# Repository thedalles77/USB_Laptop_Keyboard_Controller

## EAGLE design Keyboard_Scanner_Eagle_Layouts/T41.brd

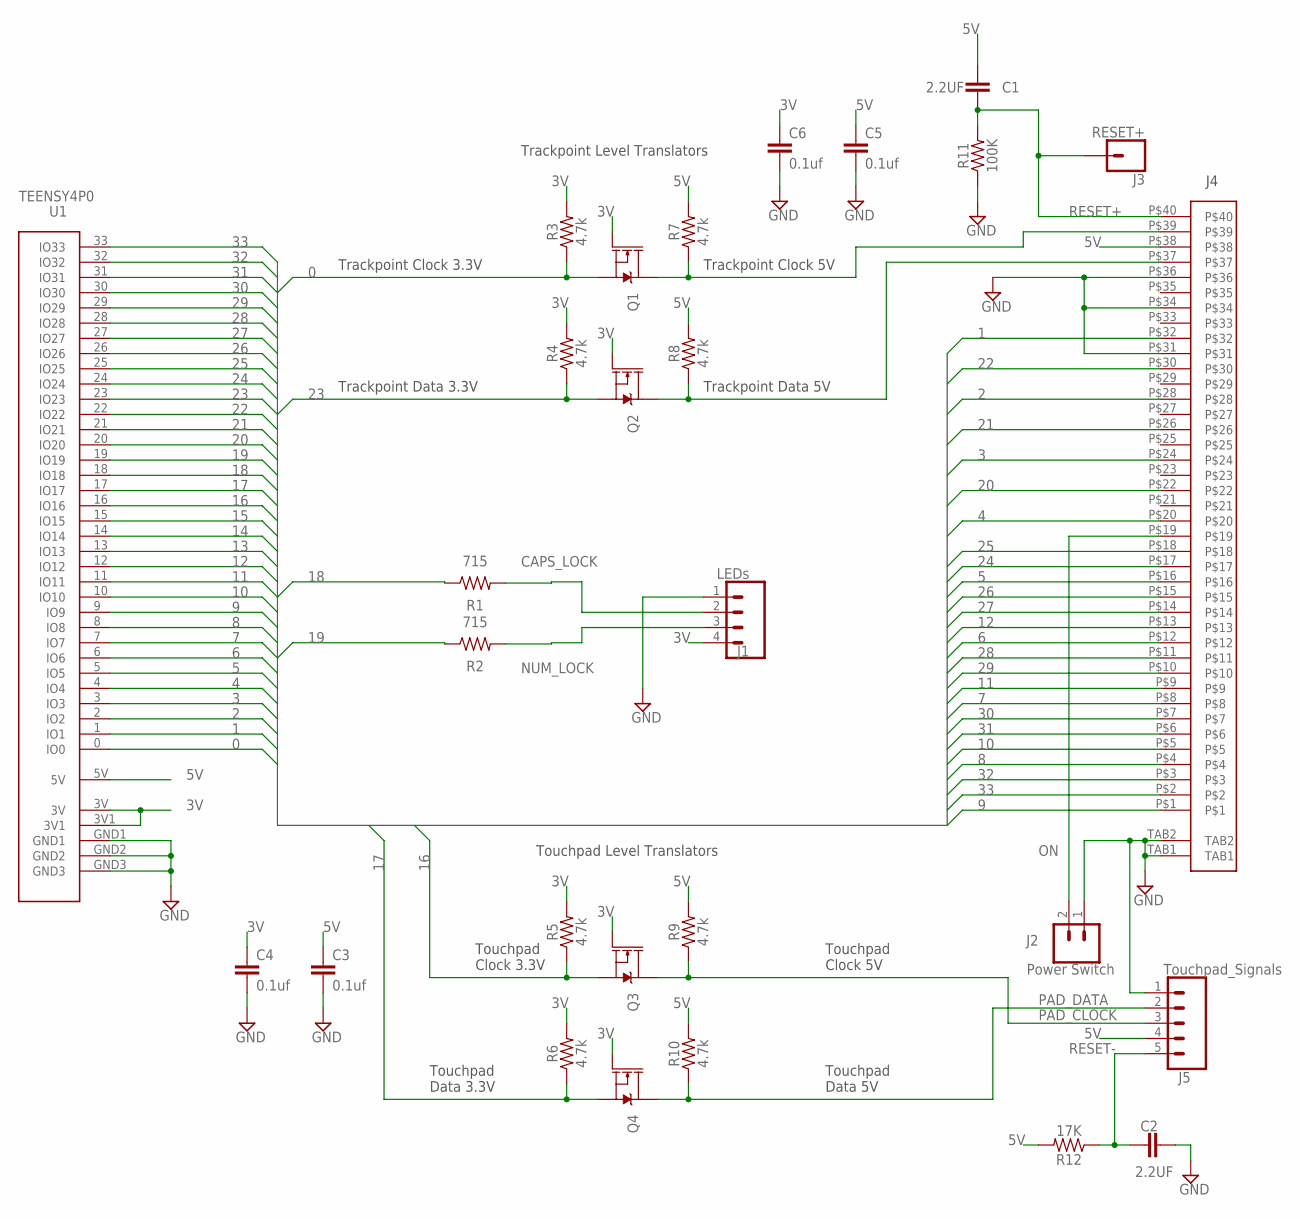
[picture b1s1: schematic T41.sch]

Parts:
C1, C2: 2.2UF; 0603_CAP
C3, C4, C5, C6: 0.1uf; 0603_CAP
J1: LEDs; 1X04
J2: Power Switch; 1X02
J3: RESET+; 1X01_NO_SILK
J4: KX14-40K5DE; KX14_40K5DE
J5: Touchpad_Signals; 1X05
Q1, Q2, Q3, Q4: 220mA/50V/3.5Ω; SOT23-3
R1, R2: 715; 0603
R3, R4, R5, R6, R7, R8, R9, R10: 4.7k; 0603
R11: 100K; 0603_RESISTOR
R12: 17K; 0603_RESISTOR
U1: TEENSY4P0

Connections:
0: Q1.2 (S), R3.1, U1.0 (IO0)
1: J4.P$32, U1.1 (IO1)
2: J4.P$28, U1.2 (IO2)
3: J4.P$24, U1.3 (IO3)
3V: C4.1, C6.1, J1.4, Q1.1 (G), Q2.1 (G), Q3.1 (G), Q4.1 (G), R3.2, R4.2, R5.2, R6.2, U1.3V, U1.3V1
4: J4.P$20, U1.4 (IO4)
5: J4.P$16, U1.5 (IO5)
5V: C1.1, C3.1, C5.1, J4.P$38, J5.4, R7.2, R8.2, R9.2, R10.2, R12.2, U1.5V
6: J4.P$12, U1.6 (IO6)
7: J4.P$8, U1.7 (IO7)
8: J4.P$4, U1.8 (IO8)
9: J4.P$1, U1.9 (IO9)
10: J4.P$5, U1.10 (IO10)
11: J4.P$9, U1.11 (IO11)
12: J4.P$13, U1.12 (IO12)
13: U1.13 (IO13)
14: U1.14 (IO14)
15: U1.15 (IO15)
16: Q3.2 (S), R5.1, U1.16 (IO16)
17: Q4.2 (S), R6.1, U1.17 (IO17)
18: R1.1, U1.18 (IO18)
19: R2.1, U1.19 (IO19)
20: J4.P$22, U1.20 (IO20)
21: J4.P$26, U1.21 (IO21)
22: J4.P$30, U1.22 (IO22)
23: Q2.2 (S), R4.1, U1.23 (IO23)
24: J4.P$17, U1.24 (IO24)
25: J4.P$18, U1.25 (IO25)
26: J4.P$15, U1.26 (IO26)
27: J4.P$14, U1.27 (IO27)
28: J4.P$11, U1.28 (IO28)
29: J4.P$10, U1.29 (IO29)
30: J4.P$7, U1.30 (IO30)
31: J4.P$6, U1.31 (IO31)
32: J4.P$3, U1.32 (IO32)
33: J4.P$2, U1.33 (IO33)
CAPS_LOCK: J1.2, R1.2
GND: C2.2, C3.2, C4.2, C5.2, C6.2, J1.1, J2.1, J4.P$31, J4.P$34, J4.P$36, J4.TAB1, J4.TAB2, J5.1, R11.1, U1.GND1, U1.GND2, U1.GND3
NUM_LOCK: J1.3, R2.2
ON: J2.2, J4.P$19
PAD_CLOCK: J5.3, Q3.3 (D), R9.1
PAD_DATA: J5.2, Q4.3 (D), R10.1
RESET+: C1.2, J3.1, J4.P$40, R11.2
RESET-: C2.1, J5.5, R12.1
TP_CLK: J4.P$39, Q1.3 (D), R7.1
TP_DATA: J4.P$37, Q2.3 (D), R8.1

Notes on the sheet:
Trackpoint Clock 3.3V
Trackpoint Data 3.3V
Trackpoint Clock 5V
Trackpoint Data 5V
Trackpoint Level Translators
Touchpad Level Translators
Touchpad Clock 3.3V
Touchpad Data 3.3V
Touchpad Clock 5V
Touchpad Data 5V

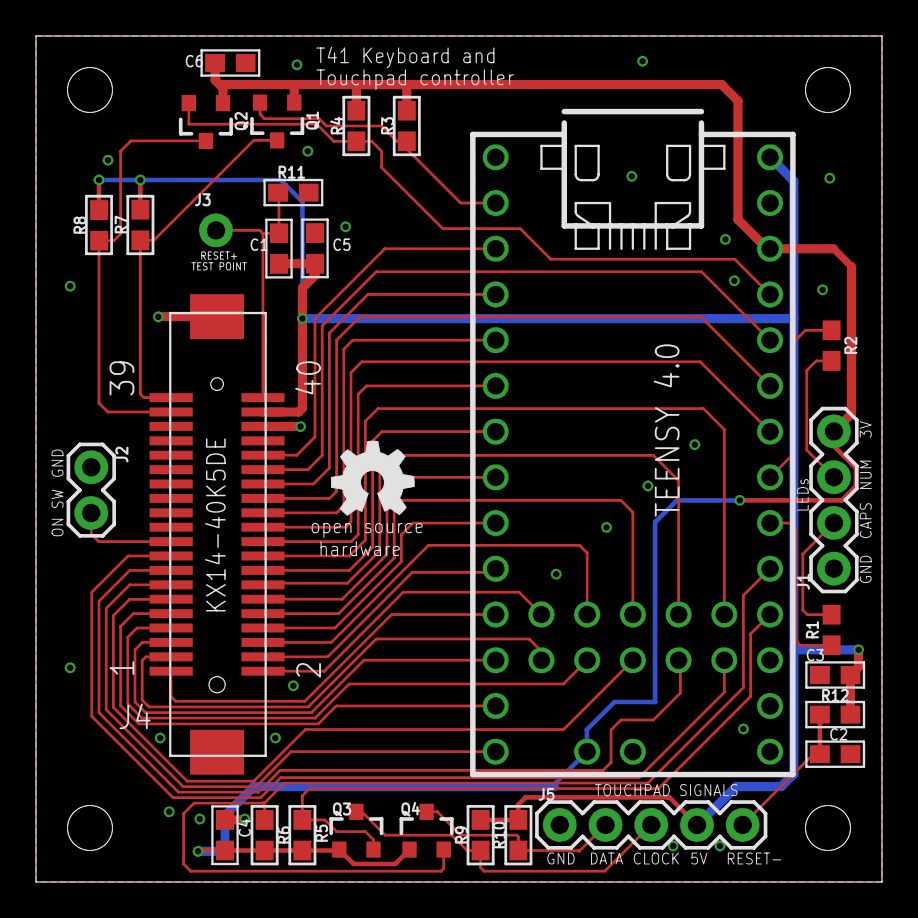
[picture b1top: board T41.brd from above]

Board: 2 copper layers, 47.0 x 47.0 mm, 29 parts (0 on the bottom side), 43 nets.

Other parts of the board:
U$1: OSHW_5MM

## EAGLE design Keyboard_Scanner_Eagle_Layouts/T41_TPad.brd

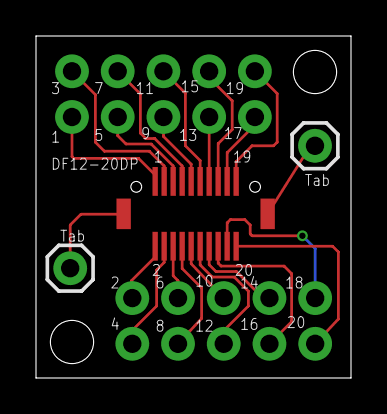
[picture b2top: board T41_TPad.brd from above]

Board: 2 copper layers, 17.5 x 19.0 mm, 5 parts (0 on the bottom side), 22 nets.

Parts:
J1: DF12-20DP
J2, J3: 2X5_NOSILK
J4, J5: 1X01

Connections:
unnamed: J1.19, J3.10
unnamed: J1.3, J3.2
unnamed: J1.1, J3.1
unnamed: J1.5, J3.3
unnamed: J1.7, J3.4
unnamed: J1.9, J3.5
unnamed: J1.11, J3.6
unnamed: J1.13, J3.7
unnamed: J1.15, J3.8
unnamed: J1.17, J3.9
unnamed: J1.2, J2.2
unnamed: J1.4, J2.1
unnamed: J1.6, J2.4
unnamed: J1.8, J2.3
unnamed: J1.10, J2.6
unnamed: J1.12, J2.5
unnamed: J1.14, J2.8
unnamed: J1.16, J2.7
unnamed: J1.18, J2.10
unnamed: J1.20, J2.9
unnamed: J1.TAB1, J4.1
unnamed: J1.TAB2, J5.1

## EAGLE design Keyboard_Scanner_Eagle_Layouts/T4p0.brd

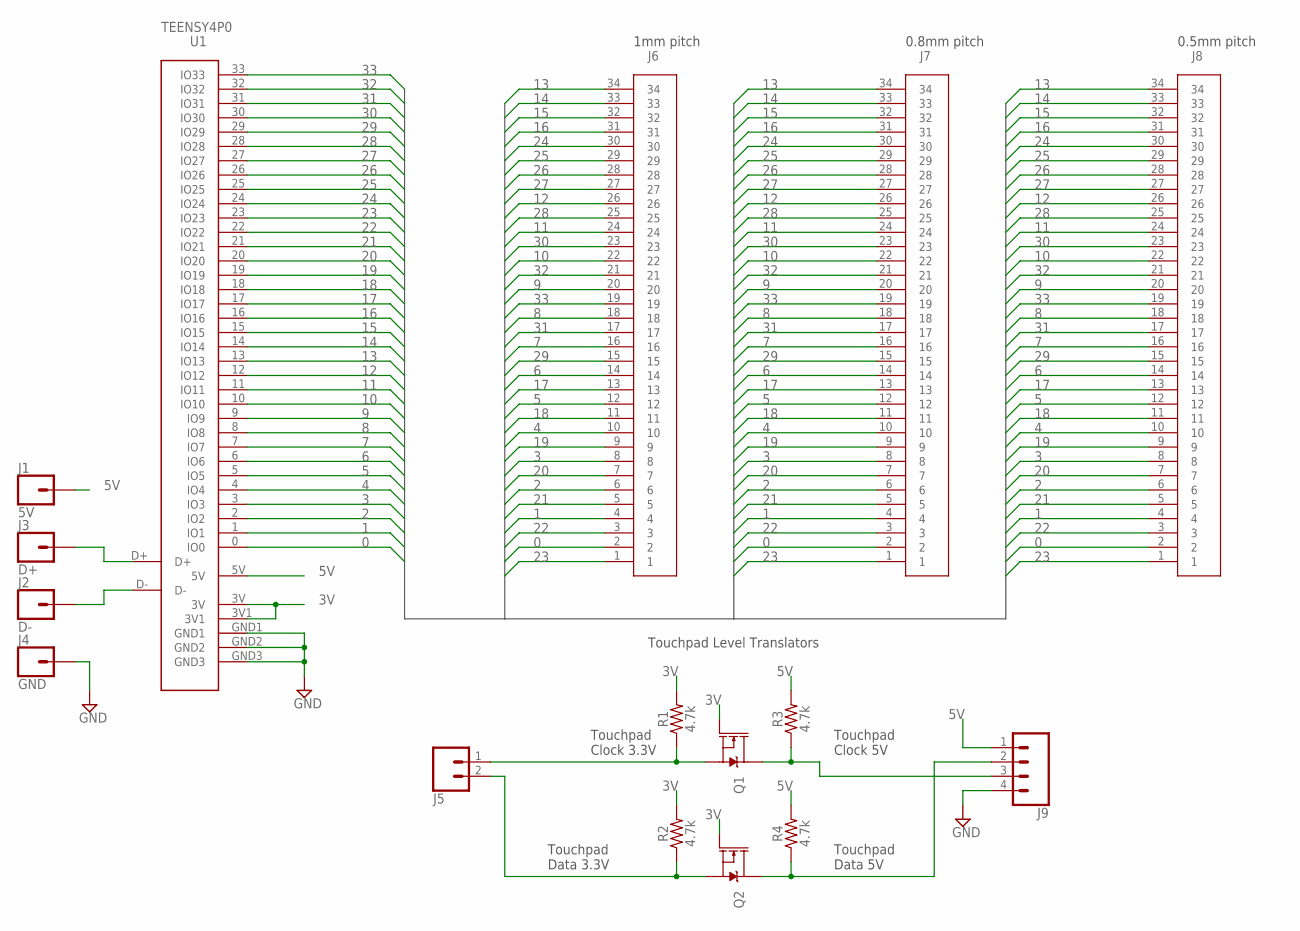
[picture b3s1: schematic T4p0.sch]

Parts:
J1: 5V; 1X01_NO_SILK
J2: D-; 1X01_NO_SILK
J3: D+; 1X01_NO_SILK
J4: GND; 1X01_NO_SILK
J5: CONN_021X02_NO_SILK; 1X02_NO_SILK
J6: FPC34
J7: FPC34_P8MM
J8: FPC34_P5MM
J9: CONN_041X04_NO_SILK; 1X04_NO_SILK
Q1, Q2: 220mA/50V/3.5Ω; SOT23-3
R1, R2, R3, R4: 4.7k; 0603
U1: TEENSY4P0

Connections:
0: J6.2, J7.2, J8.2, U1.0 (IO0)
1: J6.4, J7.4, J8.4, U1.1 (IO1)
2: J6.6, J7.6, J8.6, U1.2 (IO2)
3: J6.8, J7.8, J8.8, U1.3 (IO3)
3V: Q1.1 (G), Q2.1 (G), R1.2, R2.2, U1.3V, U1.3V1
4: J6.10, J7.10, J8.10, U1.4 (IO4)
5: J6.12, J7.12, J8.12, U1.5 (IO5)
5V: J1.1, J9.1, R3.2, R4.2, U1.5V
6: J6.14, J7.14, J8.14, U1.6 (IO6)
7: J6.16, J7.16, J8.16, U1.7 (IO7)
8: J6.18, J7.18, J8.18, U1.8 (IO8)
9: J6.20, J7.20, J8.20, U1.9 (IO9)
10: J6.22, J7.22, J8.22, U1.10 (IO10)
11: J6.24, J7.24, J8.24, U1.11 (IO11)
12: J6.26, J7.26, J8.26, U1.12 (IO12)
13: J6.34, J7.34, J8.34, U1.13 (IO13)
14: J6.33, J7.33, J8.33, U1.14 (IO14)
15: J6.32, J7.32, J8.32, U1.15 (IO15)
16: J6.31, J7.31, J8.31, U1.16 (IO16)
17: J6.13, J7.13, J8.13, U1.17 (IO17)
18: J6.11, J7.11, J8.11, U1.18 (IO18)
19: J6.9, J7.9, J8.9, U1.19 (IO19)
20: J6.7, J7.7, J8.7, U1.20 (IO20)
21: J6.5, J7.5, J8.5, U1.21 (IO21)
22: J6.3, J7.3, J8.3, U1.22 (IO22)
23: J6.1, J7.1, J8.1, U1.23 (IO23)
24: J6.30, J7.30, J8.30, U1.24 (IO24)
25: J6.29, J7.29, J8.29, U1.25 (IO25)
26: J6.28, J7.28, J8.28, U1.26 (IO26)
27: J6.27, J7.27, J8.27, U1.27 (IO27)
28: J6.25, J7.25, J8.25, U1.28 (IO28)
29: J6.15, J7.15, J8.15, U1.29 (IO29)
30: J6.23, J7.23, J8.23, U1.30 (IO30)
31: J6.17, J7.17, J8.17, U1.31 (IO31)
32: J6.21, J7.21, J8.21, U1.32 (IO32)
33: J6.19, J7.19, J8.19, U1.33 (IO33)
CLK3V: J5.1, Q1.2 (S), R1.1
CLK5V: J9.3, Q1.3 (D), R3.1
D+: J3.1, U1.D+
D-: J2.1, U1.D-
DATA3V: J5.2, Q2.2 (S), R2.1
DATA5V: J9.2, Q2.3 (D), R4.1
GND: J4.1, J9.4, U1.GND1, U1.GND2, U1.GND3

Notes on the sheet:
Touchpad Level Translators
Touchpad Clock 3.3V
Touchpad Data 3.3V
Touchpad Clock 5V
Touchpad Data 5V
1mm pitch
0.8mm pitch
0.5mm pitch

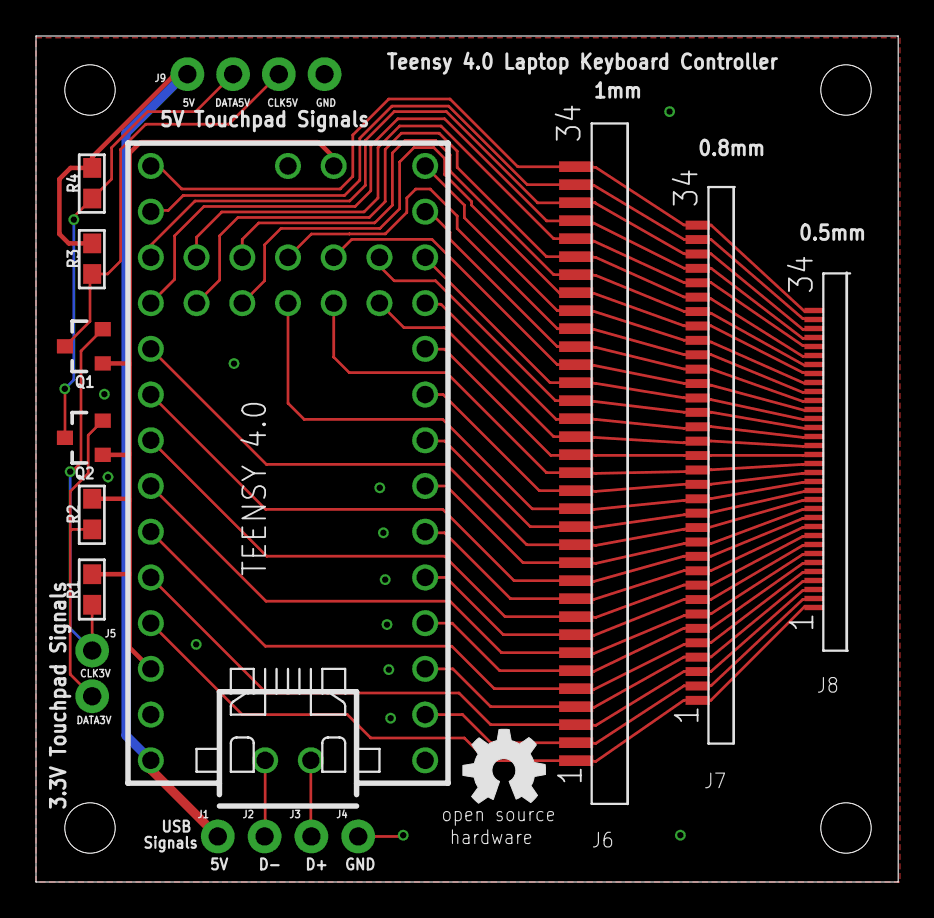
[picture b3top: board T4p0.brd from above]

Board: 2 copper layers, 47.9 x 47.0 mm, 18 parts (0 on the bottom side), 43 nets.

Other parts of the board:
U$1: OSHW_5MM
U$2: OSHW_8MM

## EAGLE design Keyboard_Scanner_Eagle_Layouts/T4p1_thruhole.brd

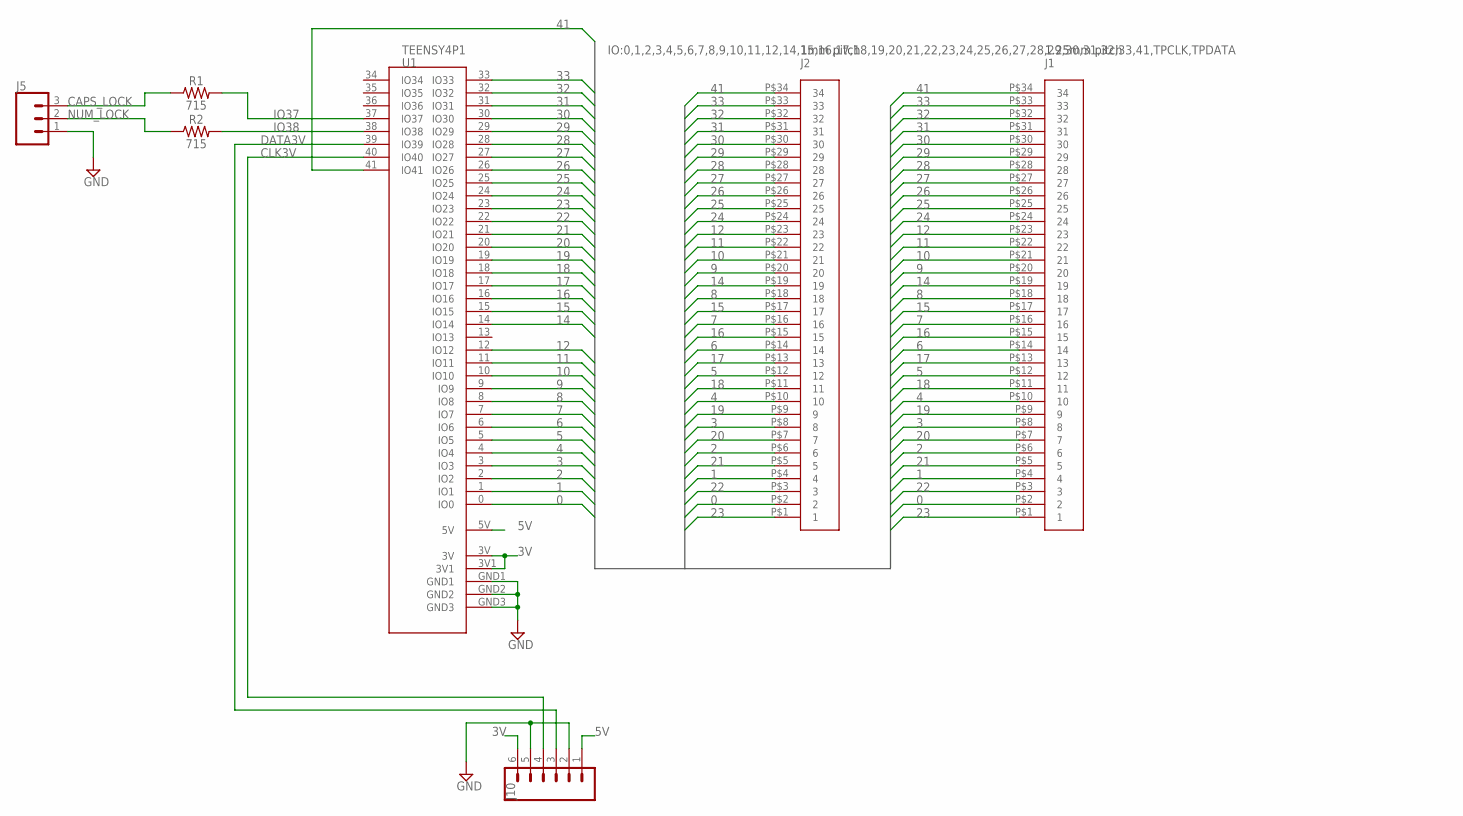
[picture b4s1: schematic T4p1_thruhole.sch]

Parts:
J1: 1P25MM_THRUHOLE
J2: 1MM_THRUHOLE
J5: CONN_031X03_NO_SILK; 1X03_NO_SILK
J10: CONN_06NO_SILK_NO_POP; 1X06_NO_SILK
R1, R2: 715; AXIAL-0.3
U1: TEENSY4P1

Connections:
0: J1.P$2 (2), J2.P$2 (2), U1.0 (IO0)
1: J1.P$4 (4), J2.P$4 (4), U1.1 (IO1)
2: J1.P$6 (6), J2.P$6 (6), U1.2 (IO2)
3: J1.P$8 (8), J2.P$8 (8), U1.3 (IO3)
3V: J10.6, U1.3V, U1.3V1
4: J1.P$10 (10), J2.P$10 (10), U1.4 (IO4)
5: J1.P$12 (12), J2.P$12 (12), U1.5 (IO5)
5V: J10.1, U1.5V
6: J1.P$14 (14), J2.P$14 (14), U1.6 (IO6)
7: J1.P$16 (16), J2.P$16 (16), U1.7 (IO7)
8: J1.P$18 (18), J2.P$18 (18), U1.8 (IO8)
9: J1.P$20 (20), J2.P$20 (20), U1.9 (IO9)
10: J1.P$21 (21), J2.P$21 (21), U1.10 (IO10)
11: J1.P$22 (22), J2.P$22 (22), U1.11 (IO11)
12: J1.P$23 (23), J2.P$23 (23), U1.12 (IO12)
14: J1.P$19 (19), J2.P$19 (19), U1.14 (IO14)
15: J1.P$17 (17), J2.P$17 (17), U1.15 (IO15)
16: J1.P$15 (15), J2.P$15 (15), U1.16 (IO16)
17: J1.P$13 (13), J2.P$13 (13), U1.17 (IO17)
18: J1.P$11 (11), J2.P$11 (11), U1.18 (IO18)
19: J1.P$9 (9), J2.P$9 (9), U1.19 (IO19)
20: J1.P$7 (7), J2.P$7 (7), U1.20 (IO20)
21: J1.P$5 (5), J2.P$5 (5), U1.21 (IO21)
22: J1.P$3 (3), J2.P$3 (3), U1.22 (IO22)
23: J1.P$1 (1), J2.P$1 (1), U1.23 (IO23)
24: J1.P$24 (24), J2.P$24 (24), U1.24 (IO24)
25: J1.P$25 (25), J2.P$25 (25), U1.25 (IO25)
26: J1.P$26 (26), J2.P$26 (26), U1.26 (IO26)
27: J1.P$27 (27), J2.P$27 (27), U1.27 (IO27)
28: J1.P$28 (28), J2.P$28 (28), U1.28 (IO28)
29: J1.P$29 (29), J2.P$29 (29), U1.29 (IO29)
30: J1.P$30 (30), J2.P$30 (30), U1.30 (IO30)
31: J1.P$31 (31), J2.P$31 (31), U1.31 (IO31)
32: J1.P$32 (32), J2.P$32 (32), U1.32 (IO32)
33: J1.P$33 (33), J2.P$33 (33), U1.33 (IO33)
41: J1.P$34 (34), J2.P$34 (34), U1.41 (IO41)
CAPS_LOCK: J5.3, R1.P$1 (1)
CLK3V: J10.4, U1.40 (IO40)
DATA3V: J10.3, U1.39 (IO39)
GND: J5.1, J10.2, J10.5, U1.GND1, U1.GND2, U1.GND3
IO37: R1.P$2 (2), U1.37 (IO37)
IO38: R2.P$2 (2), U1.38 (IO38)
NUM_LOCK: J5.2, R2.P$1 (1)

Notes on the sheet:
1mm pitch
1.25mm pitch

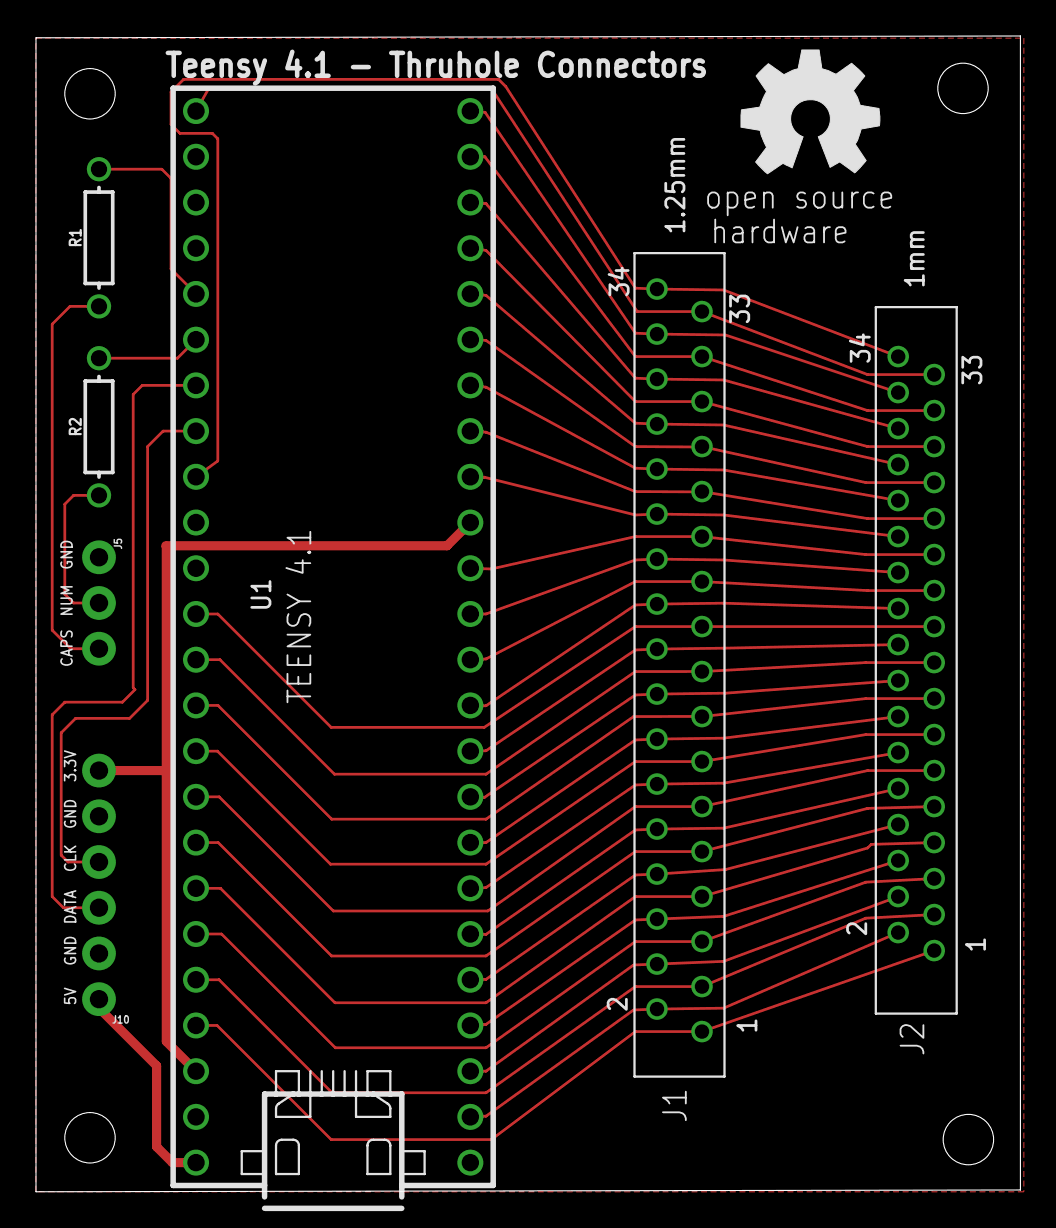
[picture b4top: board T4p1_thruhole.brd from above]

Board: 2 copper layers, 54.7 x 64.2 mm, 9 parts (0 on the bottom side), 43 nets.

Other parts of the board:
U$1, U$2: OSHW_8MM

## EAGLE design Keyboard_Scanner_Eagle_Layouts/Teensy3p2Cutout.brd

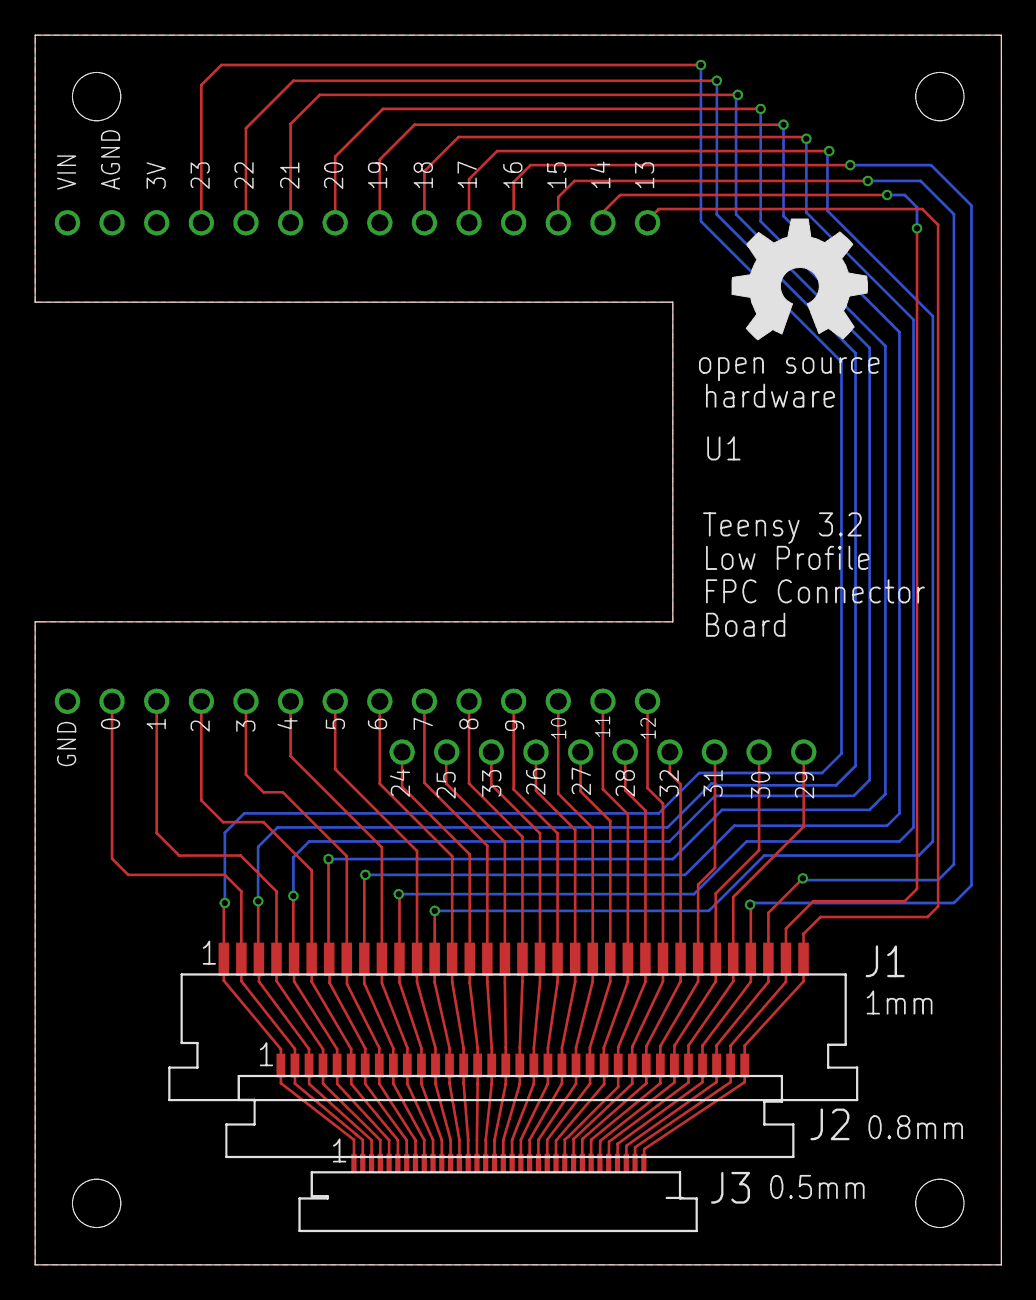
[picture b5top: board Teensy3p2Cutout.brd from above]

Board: 2 copper layers, 55.0 x 70.0 mm, 5 parts (0 on the bottom side), 34 nets.

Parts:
J1: 1mm; FPC34
J2: 0.8mm; FPC34_P8MM
J3: 0.5mm; FPC34_P5MM
U1: Teensy 3.2; TEENSY3P2CUTOUT
U$1: OSHW_8MM

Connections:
0: J1.2, J2.2, J3.2, U1.0
1: J1.4, J2.4, J3.4, U1.1
2: J1.6, J2.6, J3.6, U1.2
3: J1.8, J2.8, J3.8, U1.3
4: J1.10, J2.10, J3.10, U1.4
5: J1.12, J2.12, J3.12, U1.5
6: J1.14, J2.14, J3.14, U1.6
7: J1.16, J2.16, J3.16, U1.7
8: J1.18, J2.18, J3.18, U1.8
9: J1.20, J2.20, J3.20, U1.9
10: J1.22, J2.22, J3.22, U1.10
11: J1.24, J2.24, J3.24, U1.11
12: J1.26, J2.26, J3.26, U1.12
13: J1.34, J2.34, J3.34, U1.13
14: J1.33, J2.33, J3.33, U1.14
15: J1.32, J2.32, J3.32, U1.15
16: J1.31, J2.31, J3.31, U1.16
17: J1.13, J2.13, J3.13, U1.17
18: J1.11, J2.11, J3.11, U1.18
19: J1.9, J2.9, J3.9, U1.19
20: J1.7, J2.7, J3.7, U1.20
21: J1.5, J2.5, J3.5, U1.21
22: J1.3, J2.3, J3.3, U1.22
23: J1.1, J2.1, J3.1, U1.23
24: J1.15, J2.15, J3.15, U1.24
25: J1.17, J2.17, J3.17, U1.25
26: J1.21, J2.21, J3.21, U1.26
27: J1.23, J2.23, J3.23, U1.27
28: J1.25, J2.25, J3.25, U1.28
29: J1.30, J2.30, J3.30, U1.29
30: J1.29, J2.29, J3.29, U1.30
31: J1.28, J2.28, J3.28, U1.31
32: J1.27, J2.27, J3.27, U1.32
33: J1.19, J2.19, J3.19, U1.33

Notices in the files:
parts and their libraries:
SparkFun-Connectors: Licensing: Creative Commons ShareAlike 4.0 International - https://creativecommons.org/licenses/by-sa/4.0
